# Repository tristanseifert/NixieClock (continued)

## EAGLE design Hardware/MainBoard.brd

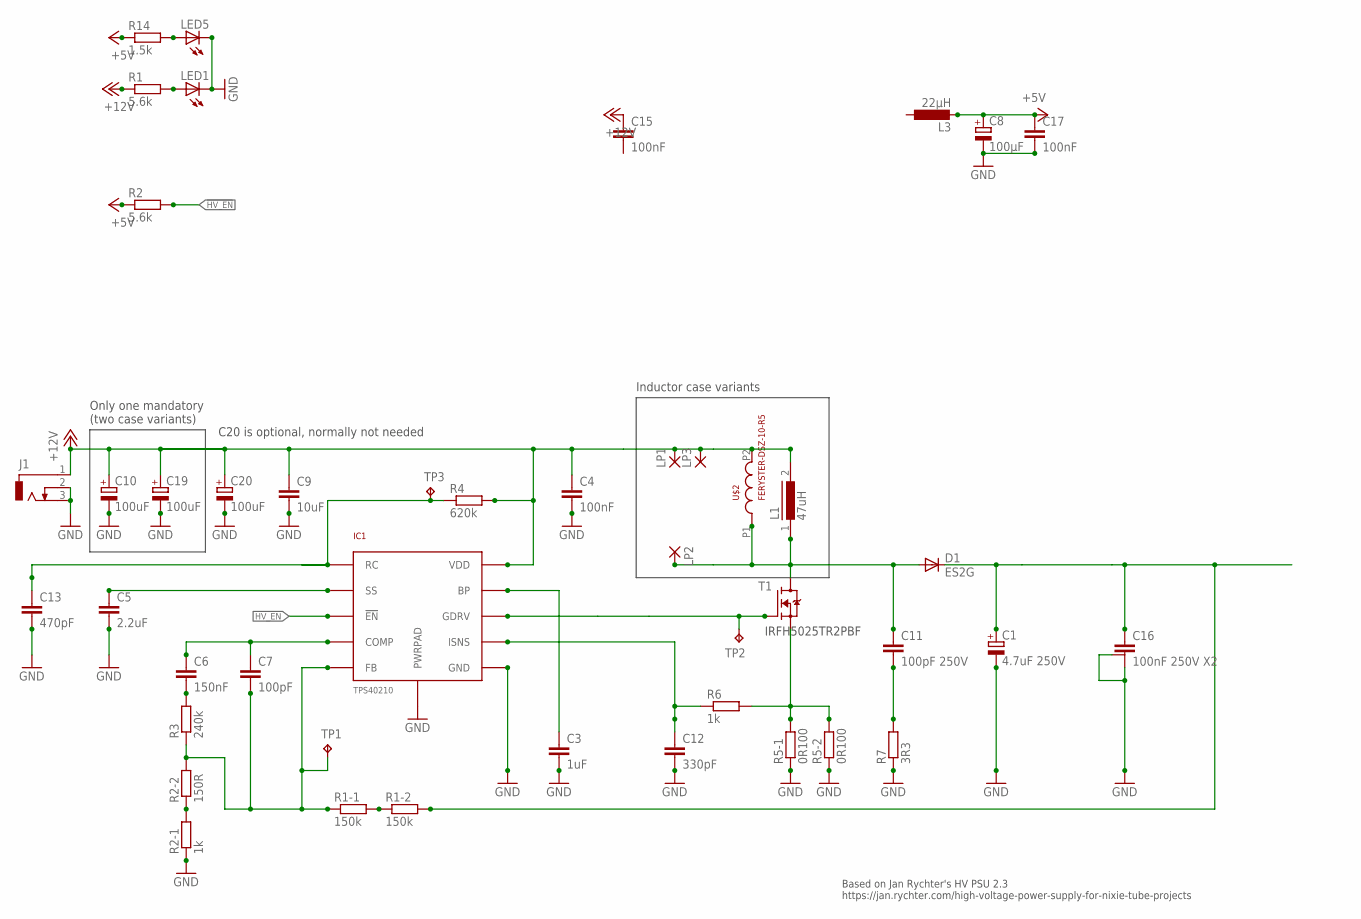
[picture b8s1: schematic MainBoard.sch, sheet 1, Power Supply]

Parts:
C1: 4.7uF 250V; E3,5-8
C3: 1uF; C0603
C4: 100nF; C0603
C5: 2.2uF; C1206
C6: 150nF; C0603
C7: 100pF; C0603
C8: 100µF; CT7343; MOUSER 581-NOSD107M006
C9: 10uF; C1206
C10, C20: 100uF; E2,5-6
C11: 100pF 250V; C1812
C12: 330pF; C0603
C13: 470pF; C0603
C15, C17: 100nF; C0805; MOUSER 710-885012207072
C16: 100nF 250V X2; C102_152-062X184
C19: 100uF; E3,5-8
D1: ES2G; DO-214AC
IC1: TPS40210DGQ; MSOP10
J1: DCJ0303
L1: 47uH; DR125
L3: 22µH; SRR1050A; MOUSER 652-SRR1050A-220Y
LED1, LED5: LEDCHIPLED_1206; CHIPLED_1206; MOUSER 604-APTR3216SGC
LP1, LP2, LP3: 3,17/1,3
R1, R2: 5.6k; M0805; MOUSER 652-CR0805FX-5601ELF
R1-1, R1-2: 150k; R0805
R2-1, R6: 1k; R0603
R2-2: 150R; R0603
R3: 240k; R0603
R4: 620k; R0603
R5-1, R5-2: 0R100; R1206
R7: 3R3; R0805
R14: 1.5k; M0805; MOUSER 652-CR0805FX-1501ELF
T1: IRFH5025PBF; PQFN5X6
TP1, TP2, TP3: TPTP08SQ; TP08SQ
U$2: FERYSTER-DSZ-10-R5; DSZ-10-R5

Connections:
!HV_EN: IC1.P$3 (!EN), R2.2; also elsewhere on the board
+5V: C8.+, C17.1, L3.P$2 (2), R2.1, R14.1; also elsewhere on the board
+12V: C4.1, C9.1, C10.+, C15.1, C19.+, C20.+, IC1.P$10 (VDD), J1.1, L1.2, LP1.1, LP3.1, R1.1, R4.2, U$2.P2; also elsewhere on the board
COMP: C6.1, C7.1, IC1.P$4 (COMP)
D: R5-1.2, R5-2.2, R6.2, T1.S1 (S), T1.S2 (S), T1.S3 (S), T1.S4 (S)
FB: C7.2, IC1.P$5 (FB), R1-1.1, R2-2.2, R3.1, TP1.TP
GDRV: IC1.P$8 (GDRV), T1.G, TP2.TP
GND: C1.-, C3.2, C4.2, C5.2, C8.-, C9.2, C10.-, C12.2, C13.2, C16.2, C16.3, C17.2, C19.-, C20.-, IC1.P$6 (GND), IC1.PWRPAD, J1.2, J1.3, LED1.C, LED5.C, R2-1.1, R5-1.1, R5-2.1, R7.1; also elsewhere on the board
HV: C1.+, C16.1, D1.C, R1-2.2; also elsewhere on the board
unnamed: LED5.A, R14.2
unnamed: LED1.A, R1.2
unnamed: R1-1.2, R1-2.1
unnamed: C13.1, IC1.P$1 (RC), R4.1, TP3.TP
unnamed: C3.1, IC1.P$9 (BP)
unnamed: C6.2, R3.2
unnamed: R2-1.2, R2-2.1
unnamed: C5.1, IC1.P$2 (SS)
unnamed: C11.2, R7.2
PULSE: C11.1, D1.A, L1.1, LP2.1, T1.D1 (D), T1.D2 (D), T1.D3 (D), T1.D4 (D), T1.D5 (D), U$2.P1
SNS: C12.1, IC1.P$7 (ISNS), R6.1

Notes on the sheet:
Only one mandatory (two case variants)
C20 is optional, normally not needed
Inductor case variants
IRFH5025TR2PBF
Based on Jan Rychter's HV PSU 2.3 https://jan.rychter.com/high-voltage-power-supply-for-nixie-tube-projects

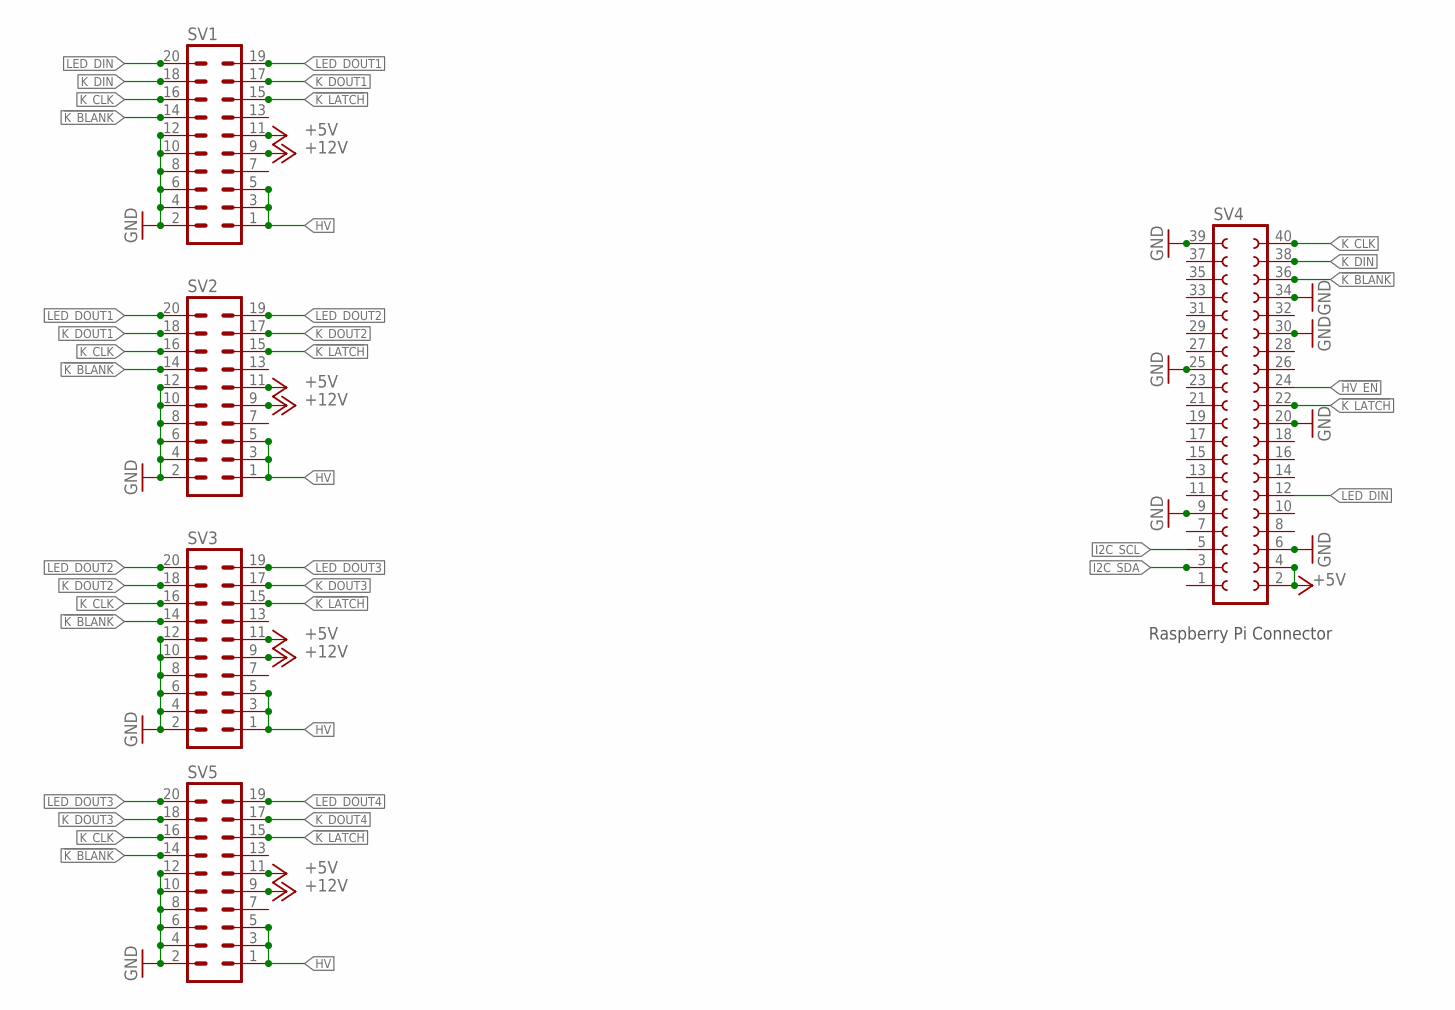
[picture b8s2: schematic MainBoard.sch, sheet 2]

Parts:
SV1, SV2, SV3, SV5: MA10-2
SV4: FE20-2

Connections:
!HV_EN: SV4.24; also elsewhere on the board
!K_BLANK: SV1.14, SV2.14, SV3.14, SV4.36, SV5.14
!K_LATCH: SV1.15, SV2.15, SV3.15, SV4.22, SV5.15
+5V: SV1.11, SV2.11, SV3.11, SV4.2, SV4.4, SV5.11; also elsewhere on the board
+12V: SV1.9, SV2.9, SV3.9, SV5.9; also elsewhere on the board
GND: SV1.2, SV1.4, SV1.6, SV1.8, SV1.10, SV1.12, SV2.2, SV2.4, SV2.6, SV2.8, SV2.10, SV2.12, SV3.2, SV3.4, SV3.6, SV3.8, SV3.10, SV3.12, SV4.6, SV4.9, SV4.20, SV4.25, SV4.30, SV4.34, SV4.39, SV5.2, SV5.4, SV5.6, SV5.8, SV5.10, SV5.12; also elsewhere on the board
HV: SV1.1, SV1.3, SV1.5, SV2.1, SV2.3, SV2.5, SV3.1, SV3.3, SV3.5, SV5.1, SV5.3, SV5.5; also elsewhere on the board
I2C_SCL: SV4.5
I2C_SDA: SV4.3
K_CLK: SV1.16, SV2.16, SV3.16, SV4.40, SV5.16
K_DIN: SV1.18, SV4.38
K_DOUT1: SV1.17, SV2.18
K_DOUT2: SV2.17, SV3.18
K_DOUT3: SV3.17, SV5.18
K_DOUT4: SV5.17
LED_DIN: SV1.20, SV4.12
LED_DOUT1: SV1.19, SV2.20
LED_DOUT2: SV2.19, SV3.20
LED_DOUT3: SV3.19, SV5.20
LED_DOUT4: SV5.19

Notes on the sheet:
Raspberry Pi Connector

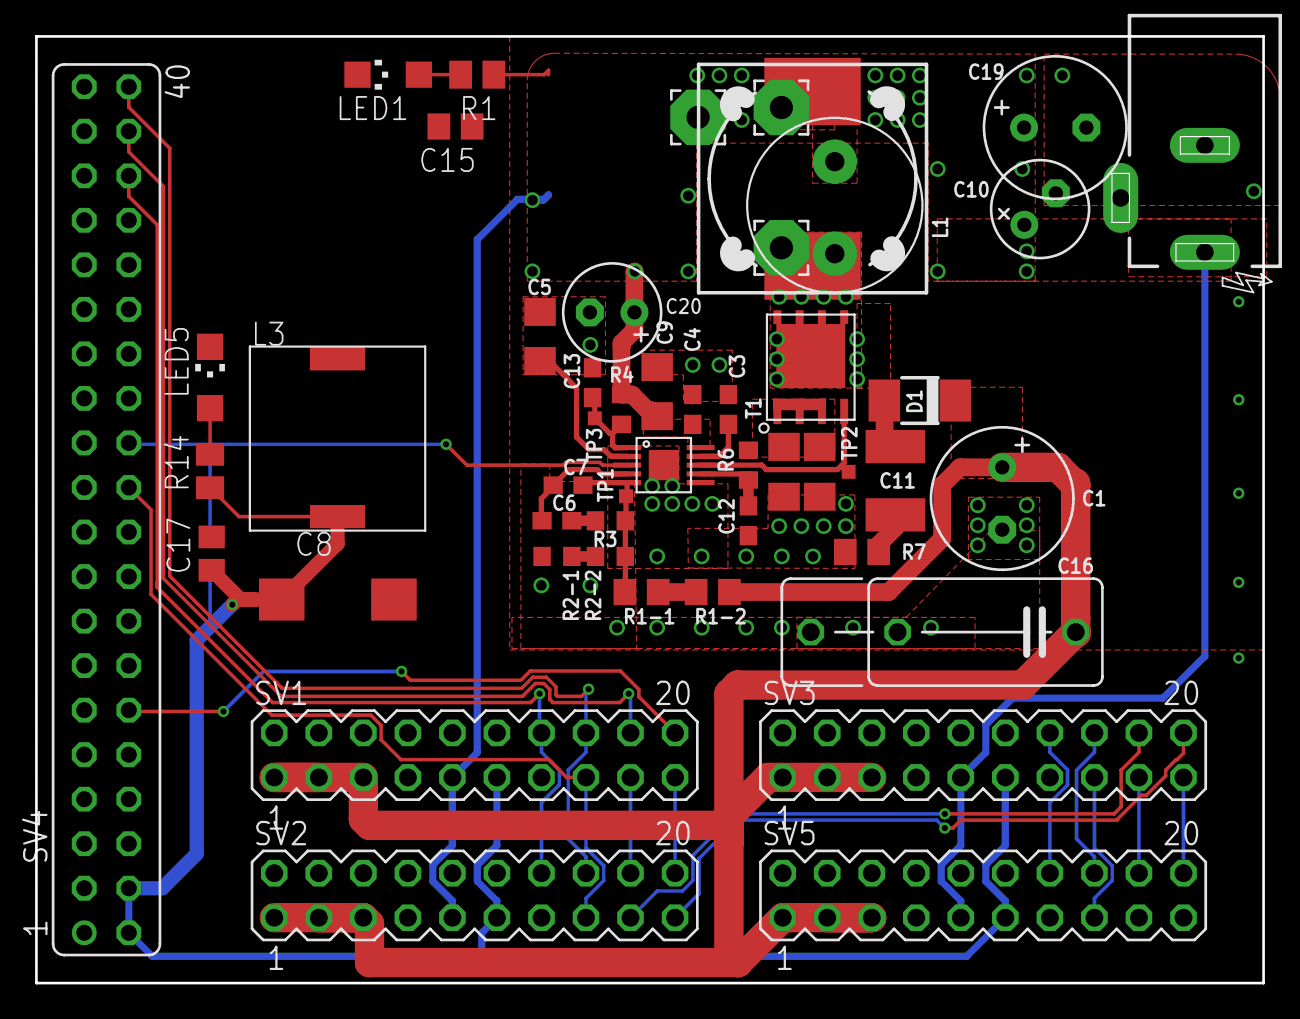
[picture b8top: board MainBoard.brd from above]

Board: 2 copper layers, 70.0 x 54.0 mm, 51 parts (1 on the bottom side), 31 nets.

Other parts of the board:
U$5: DANGER-SIGN-1X

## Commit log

2018-09-15 added shift register-based nixie driver
2018-09-15 Finished routing tube board
2018-09-15 Added hex level shifter
2018-09-15 Added readme
2018-09-15 Added colons
2018-09-22 add main board
2018-12-14 Began work on 68k-based nixie clock
2019-03-05 move files around
2019-03-06 Replaced 68681 with FT245R; added header for VFD
2019-03-06 basic address decoding
2019-03-06 use cpld for all system logic
2019-03-06 replaced SRAM with DIP variant
2019-03-06 start board layout
2019-03-07 more progress routing board
2019-03-07 added some more missing pull resistors for usb
2019-03-07 more routing of address bus
2019-03-07 cleaned up routing of busses for memories
2019-03-07 replaced cpld with ttl logic
2019-03-07 routed most system control signals
2019-03-11 routed 68681 data bus, some chip selects
2019-03-12 finished routing main board
2019-03-12 basic loader and app code
2019-03-12 added missing pull-ups to ROM and RAM CS; 68681 DTACK
2019-03-12 finished tube board schematic
2019-03-13 added transistors to drive colons
2019-03-13 separated tubes and logic on two separate boards
2019-03-14 routed tube logic board
2019-03-14 added data bus resistors; better reset circuit
2019-03-14 basic nixie routines; build a full ROM image
2019-03-15 basic 68681 initialization; more nixie driver routines and ram defines
2019-03-15 tied unused logic on tube board logic board to ground
2019-03-15 updated rom/ram chip select logic
2019-03-15 start of loader API
2019-03-16 more basic loader api
2019-03-17 revamped power connections; moved power regulation to separate board (plus RS232 conversion)
2019-03-21 Added HV supply; cleaned up power board
2019-03-26 added ARM chip to driver boards to PWM tubes
2019-03-28 added pwm drivers to tube board
2019-03-31 basic rtc routines
2019-04-01 basic 68681 init
2019-04-01 more uart stuff in loader
2019-04-02 more work on 68681 support; basic loader menu
2019-04-05 basic app and updated checksum handling
2019-04-06 finished checksum tool
2019-04-07 more work for vfd command handling
2019-04-07 began working on emulator for loader/app code
2019-04-07 switch to using musashi for 68k emulation
2019-04-08 Fixed bug preventing output in loader; began work on 68681 emulation
2019-04-08 more work on 68681 emulation
2019-04-10 more mc68681 emulation things
2019-04-10 semi functional 68681 emulation (enough to get UART A working)
2019-04-10 use RESET as a software interrupt
2019-04-11 basic tube drivers IO
2019-04-12 basic implementation of rtc/vfd to have no more unmapped memory accesses
2019-04-13 DS1244 pattern recognition
2019-04-21 more routing of tube logic board
2019-04-28 finished routing basic data latch only tube logic board
